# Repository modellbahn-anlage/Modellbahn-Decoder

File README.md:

# Modellbahn-Decoder
Ablage all unserer Modellbahn-Decoder

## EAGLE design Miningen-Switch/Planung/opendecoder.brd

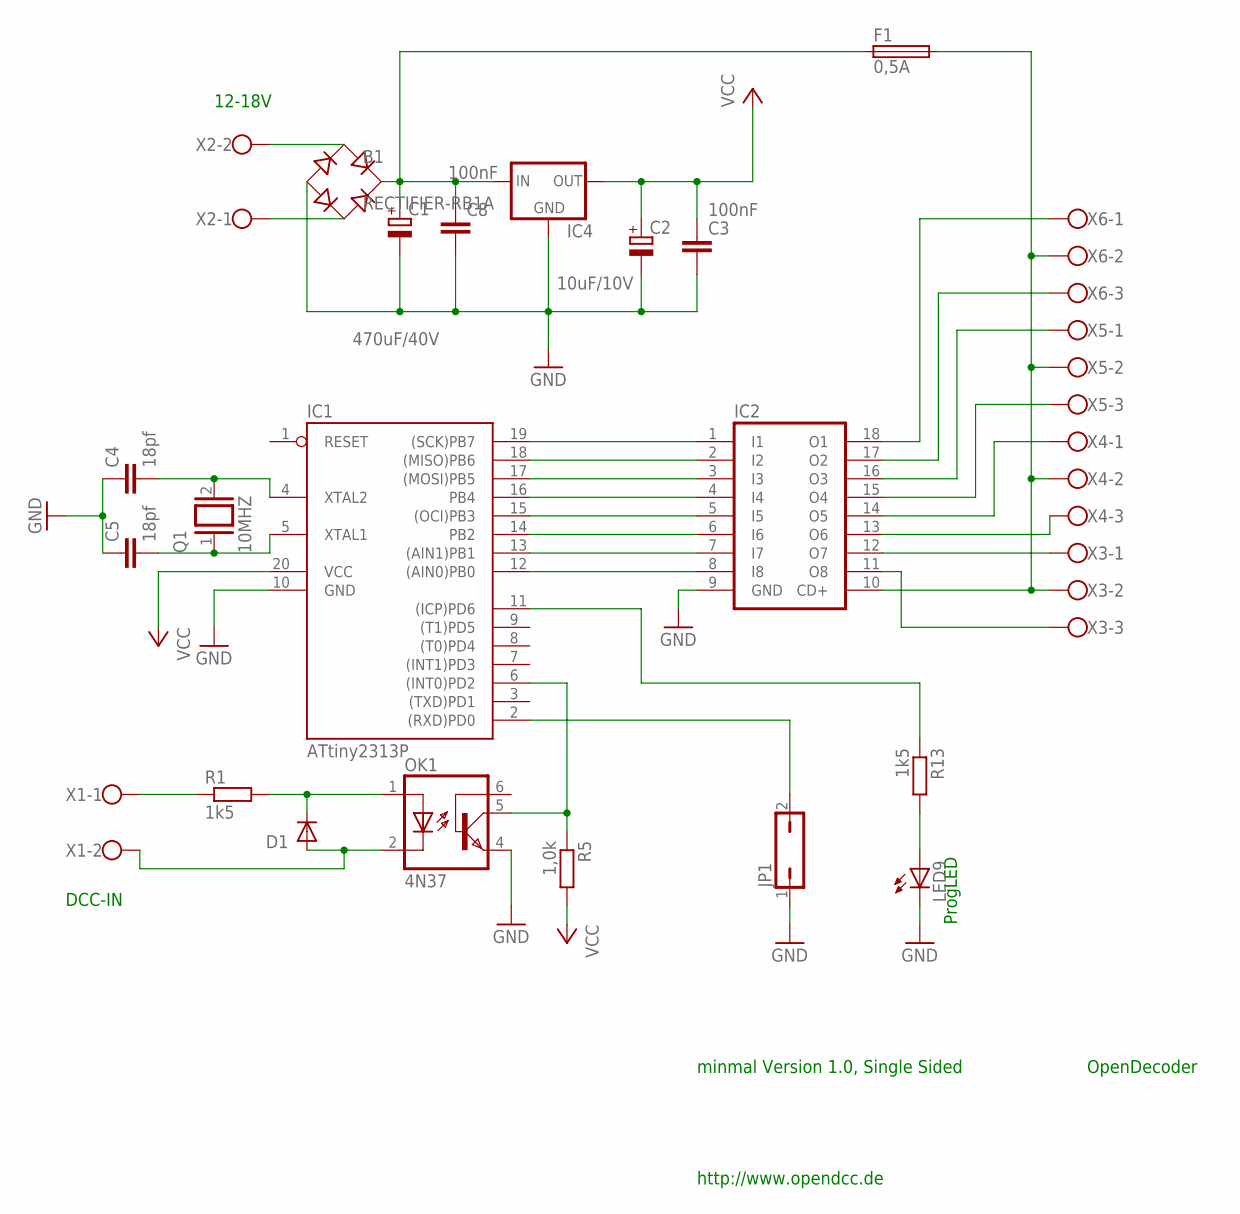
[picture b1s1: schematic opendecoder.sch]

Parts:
B1: RECTIFIER-RB1A; RB1A
C1: 470uF/40V; E5-10,5
C2: 10uF/10V; E5-6
C3: 100nF; C025_050-025X075
C4, C5: 18pf; C025-025X050
C8: 100nF; C050-024X044
D1: DIODE-D-2.5; D-2.5
F1: 0,5A; TE5
IC1: ATtiny2313P; DIL20
IC2: ULN2803A; DIL18
IC4: 78XXS
JP1: JP1Q; JP1
LED9: LED3MM
OK1: 4N37; DIL06
Q1: 10MHZ; QS
R1, R13: 1k5; 0204V
R5: 1,0k; 0207/2V
X1, X2: AK550/2
X3, X4, X5, X6: AK550/3

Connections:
GND: B1.-, C1.-, C2.-, C3.2, C4.1, C5.1, C8.2, IC1.10 (GND), IC2.9 (GND), IC4.GND, JP1.1, LED9.K (C), OK1.4 (EMI)
unnamed: IC1.19 ((SCK)PB7), IC2.1 (I1)
unnamed: IC2.16 (O3), X5.1
unnamed: B1.AC1, X2.2
unnamed: B1.AC2, X2.1
unnamed: IC1.18 ((MISO)PB6), IC2.2 (I2)
unnamed: IC1.17 ((MOSI)PB5), IC2.3 (I3)
unnamed: IC1.6 ((INT0)PD2), OK1.5 (COL), R5.1
unnamed: D1.A, OK1.2 (C), X1.2
unnamed: R1.1, X1.1
unnamed: IC1.16 (PB4), IC2.4 (I4)
unnamed: IC1.15 ((OCI)PB3), IC2.5 (I5)
unnamed: IC1.14 (PB2), IC2.6 (I6)
unnamed: IC1.13 ((AIN1)PB1), IC2.7 (I7)
unnamed: IC1.12 ((AIN0)PB0), IC2.8 (I8)
unnamed: IC2.17 (O2), X6.3
unnamed: B1.+, C1.+, C8.1, F1.1, IC4.IN
unnamed: IC2.11 (O8), X3.3
unnamed: IC2.13 (O6), X4.3
unnamed: IC2.12 (O7), X3.1
unnamed: IC2.14 (O5), X4.1
unnamed: IC2.15 (O4), X5.3
unnamed: IC2.18 (O1), X6.1
unnamed: F1.2, IC2.10 (CD+), X3.2, X4.2, X5.2, X6.2
unnamed: C4.2, IC1.4 (XTAL2), Q1.2
unnamed: C5.2, IC1.5 (XTAL1), Q1.1
unnamed: D1.C, OK1.1 (A), R1.2
unnamed: IC1.2 ((RXD)PD0), JP1.2
unnamed: IC1.11 ((ICP)PD6), R13.1
unnamed: LED9.A, R13.2
VCC: C2.+, C3.1, IC1.20 (VCC), IC4.OUT, R5.2

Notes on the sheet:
12-18V
DCC-IN
OpenDecoder
minmal Version 1.0, Single Sided
http://www.opendcc.de
ProgLED

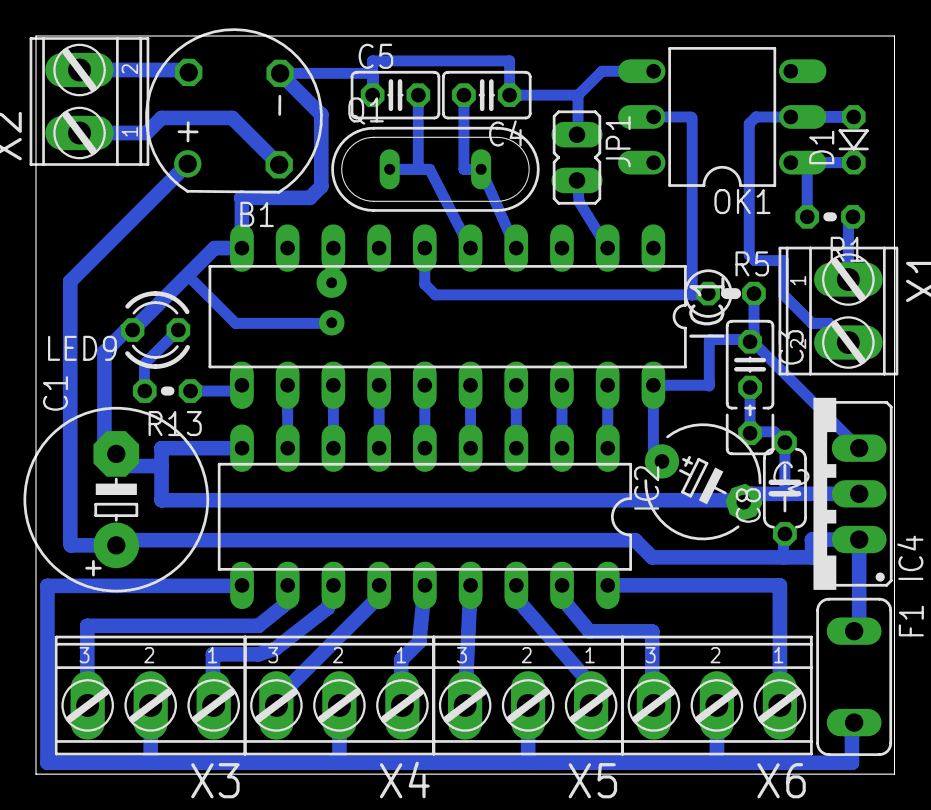
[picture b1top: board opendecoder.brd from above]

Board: 2 copper layers, 47.7 x 41.0 mm, 25 parts (0 on the bottom side), 31 nets.

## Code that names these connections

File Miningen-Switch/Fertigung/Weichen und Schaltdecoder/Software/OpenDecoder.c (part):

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            #define AMP_BL  ( 500000L / TICK_PERIOD)   // Blinken
             if (myCommand == 0) // = schalte auf rot
               {
                      output(PB0,0);  // rot
                      out_pwm[0].rest    = AMP_YE;
                      out_pwm[0].ontime  = 0;
                    
                      output(PB1,1);
                      out_pwm[1].rest    = AMP_YE;
                      out_pwm[1].offtime = 0;
                    
                      output(PB2,0);   // grün
                      out_pwm[2].rest    = 0;
                      
                      output(PB3,0);   // StopMagnet nach halber Gelb ein
                      out_pwm[3].rest    = AMP_YE / 2;
                      out_pwm[3].ontime = 0;                   
               }
             else if (myCommand == 1) // = schalte auf grün
               {
                      output(PB0,1);  // rot
                      out_pwm[0].rest    = AMP_YE;
                      out_pwm[0].offtime  = 0;
                    
                      output(PB1,1);
                      out_pwm[1].rest    = AMP_YE;
                      out_pwm[1].offtime = 0;
                    
                      output(PB2,0);   // grün
                      out_pwm[2].rest    = AMP_YE;
                      out_pwm[2].ontime = 0;                      

                      output(PB3,1);   // Magnet nach 1,5 gelb aus
                      out_pwm[3].rest    = 3*AMP_YE / 2;
                      out_pwm[3].offtime = 0;                   
               }
             else if (myCommand == 2) // = alles aus
               {
                      output(PB1,0);
                      out_pwm[1].rest    = 0;
                      output(PB0,0);
                      out_pwm[0].rest    = 0;
                      output(PB2,0);
                      out_pwm[2].rest    = 0;
                      output(PB3,0);
                      out_pwm[3].rest    = 0;
               }                     
             else if (myCommand == 3) // blinken
               {
                      output(PB1,1);
                      out_pwm[1].rest    = AMP_YE;
                      out_pwm[1].ontime  = AMP_YE;
                      out_pwm[1].offtime = AMP_YE;
                      output(PB0,0);
                      out_pwm[0].rest    = 0;
                      output(PB2,0);
                      out_pwm[2].rest    = 0;
                      output(PB3,0);
                      out_pwm[3].rest    = 0;
               }
             else if (myCommand == 4) // = schalte auf rot
               {
                      output(PB4,0);  // rot
                      out_pwm[4].rest    = AMP_YE;
                      out_pwm[4].ontime  = 0;
                    
                      output(PB5,1);
                      out_pwm[5].rest    = AMP_YE;
                      out_pwm[5].offtime = 0;
                    
                      output(PB6,0);   // grün
                      out_pwm[6].rest    = 0;
                      
                      output(PB7,0);   // Magnet
                      out_pwm[7].rest    = AMP_YE / 2;
                      out_pwm[7].ontime = 0;                   
               }
             else if (myCommand == 5) // = schalte auf grün
               {
                      output(PB4,1);  // rot
                      out_pwm[4].rest    = AMP_YE;
                      out_pwm[4].offtime  = 0;
                    
                      output(PB5,1);
                      out_pwm[5].rest    = AMP_YE;
                      out_pwm[5].offtime = 0;
                    
                      output(PB6,0);   // grün
                      out_pwm[6].rest    = AMP_YE;
                      out_pwm[6].ontime = 0;                      

                      output(PB7,1);   // Magnet
                      out_pwm[7].rest    = 3*AMP_YE / 2;
                      out_pwm[7].offtime = 0;                   

               }
             else if (myCommand == 6) // = alles aus
               {
                      output(PB5,0);
                      out_pwm[5].rest    = 0;
                      output(PB4,0);
                      out_pwm[4].rest    = 0;
                      output(PB6,0);
                      out_pwm[6].rest    = 0;
                      output(PB7,0);
                      out_pwm[7].rest    = 0;
               }                     
             else // (myCommand == 7) // blinken
               {
                      output(PB5,1);
                      out_pwm[5].rest    = AMP_YE;
                      out_pwm[5].ontime  = AMP_YE;
                      out_pwm[5].offtime = AMP_YE;
                      output(PB4,0);
                      out_pwm[4].rest    = 0;
                      output(PB6,0);
                      out_pwm[6].rest    = 0;
                      output(PB7,0);
                      out_pwm[7].rest    = 0;
               }             
          }
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;
            if (myCommand == 0)
              {
                    output(PB3,0);
                    output(PB2,0);
                    output(PB1,0);
                    output(PB0,1);
               }
            else if (myCommand == 1)
               {
                    output(PB3,0);
                    output(PB2,0);
                    output(PB1,1);
                    output(PB0,0);
               }
             else if (myCommand == 2)
               {
                    output(PB3,0);
                    output(PB2,1);
                    output(PB1,0);
                    output(PB0,0);
               }
             else if (myCommand == 3)
               {
                    output(PB3,1);
                    output(PB2,0);
                    output(PB1,0);
                    output(PB0,0);
               }
             else if (myCommand == 4)
               {
                    output(PB4,1);
                    output(PB5,0);
                    output(PB6,0);
                    output(PB7,0);
               }
             else if (myCommand == 5)
               {
                    output(PB4,0);
                    output(PB5,1);
                    output(PB6,0);
                    output(PB7,0);
               }
             else if (myCommand == 6)
               {
                    output(PB4,0);
                    output(PB5,0);
                    output(PB6,1);
                    output(PB7,0);
               }
             else // (myCommand == 7)
               {
                    output(PB4,0);
                    output(PB5,0);
                    output(PB6,0);
                    output(PB7,1);
               }       

          }
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            
            if (myCommand == 0)
              {
                    output(PB2,0);
                    output(PB1,0);
                    output(PB0,1);
                }
            else if (myCommand == 1)
               {
                    output(PB2,0);
                    output(PB1,1);
                    output(PB0,0);
               }
             else if (myCommand == 2)
               {
                    output(PB2,1);
                    output(PB1,0);
                    output(PB0,0);
                }
             else if (myCommand == 3)
               {
                    output(PB3,1);
                    output(PB4,0);
                    output(PB5,0);
                }
             else if (myCommand == 4)
               {
                    output(PB3,0);
                    output(PB4,1);
                    output(PB5,0);
               }
             else if (myCommand == 5)
               {
                    output(PB3,0);
                    output(PB4,0);
                    output(PB5,1);
               }
             else if (myCommand == 6)
               {
                    output(PB6,1);
                    output(PB7,0);
               }
             else // (myCommand == 7)
               {
                    output(PB6,0);
                    output(PB7,1);
               }       
          }
        else if (MyOpMode == 4)
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             
             if (myCommand == 0)
               {
                    output(PB1,0);         
                    output(PB0,1);
               }
             else if (myCommand == 1)
               {
                    output(PB1,1); 
                    output(PB0,0);
               }
             else if (myCommand == 2)
               {
                    output(PB2,1);
                    output(PB3,0);      
               }
             else if (myCommand == 3)
               {
                    output(PB2,0);
                    output(PB3,1);     
               }
             else if (myCommand == 4)
               {
                    output(PB4,1);
                    output(PB5,0);
                 }
             else if (myCommand == 5)
               {
                    output(PB4,0);
                    output(PB5,1);
               }
             else if (myCommand == 6)
               {
                    output(PB6,1);
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

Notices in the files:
Miningen-Switch/Fertigung/Weichen und Schaltdecoder/Software/OpenDecoder.c:
Copyright (c) 2006 Kufer
This source file is subject of the GNU general public license 2,
that is available at the world-wide-web at
http://www.gnu.org/licenses/gpl.txt
